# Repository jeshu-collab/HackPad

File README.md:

# HackPad1

HackPad1 is a custom 9-key macropad built using the Seeed XIAO RP2040. It includes a rotary encoder, a 128x32 OLED display, and per-key RGB lighting. The firmware is written using KMK, making it easy to customize key mappings and add new features.

This project was designed from scratch, including the PCB, enclosure, and firmware.

---

## Features

- 9-key mechanical macropad (3x3 layout)
- EC11 rotary encoder for volume control
- 128x32 OLED display
- Per-key RGB using SK6812MINI-E LEDs
- Powered by Seeed XIAO RP2040
- KMK firmware for easy customization
- Custom 2-piece 3D printed enclosure

---

## CAD Model

The enclosure is designed as a two-piece case.

- **Top Shell:** Holds the switches and has the outer frame.
- **Bottom Plate:** Closes the enclosure and supports the PCB.

### Overall View

### Case Assembly

---

## PCB

The PCB was designed in KiCad. It includes the switch matrix, rotary encoder, OLED display connections, RGB LEDs, and the XIAO RP2040.

### Schematic

### PCB Layout

---

## Firmware

The firmware is based on **KMK**.

Current functionality:

- Rotary encoder controls system volume.
- Pressing the encoder mutes/unmutes the audio.
- The 9 keys are currently mapped as number keys (1–9).
- OLED displays a startup message.

Key mappings can be easily changed by editing `main.py`.

---

## Bill of Materials (BOM)

| Component | Quantity |
|-----------|---------:|
| Cherry MX Switches | 9 |
| Keycaps | 9 |
| 1N4148 Diodes | 9 |
| SK6812MINI-E RGB LEDs | 9 |
| 0.91" 128x32 OLED Display | 1 |
| EC11 Rotary Encoder | 1 |
| Seeed XIAO RP2040 | 1 |
| 3D Printed Enclosure | 1 Set |
| M3 Screws *(update after final assembly)* | As Required |

---

## Future Improvements

- Add multiple layers and shortcuts
- OLED status indicators
- RGB lighting effects
- VIA/Vial-style configuration (if supported)
- Improve case design after testing the first prototype

---

## Acknowledgements

This project was built as part of the Hack Club HackPad initiative.

Special thanks to the Hack Club community for the resources and guidance throughout the build.

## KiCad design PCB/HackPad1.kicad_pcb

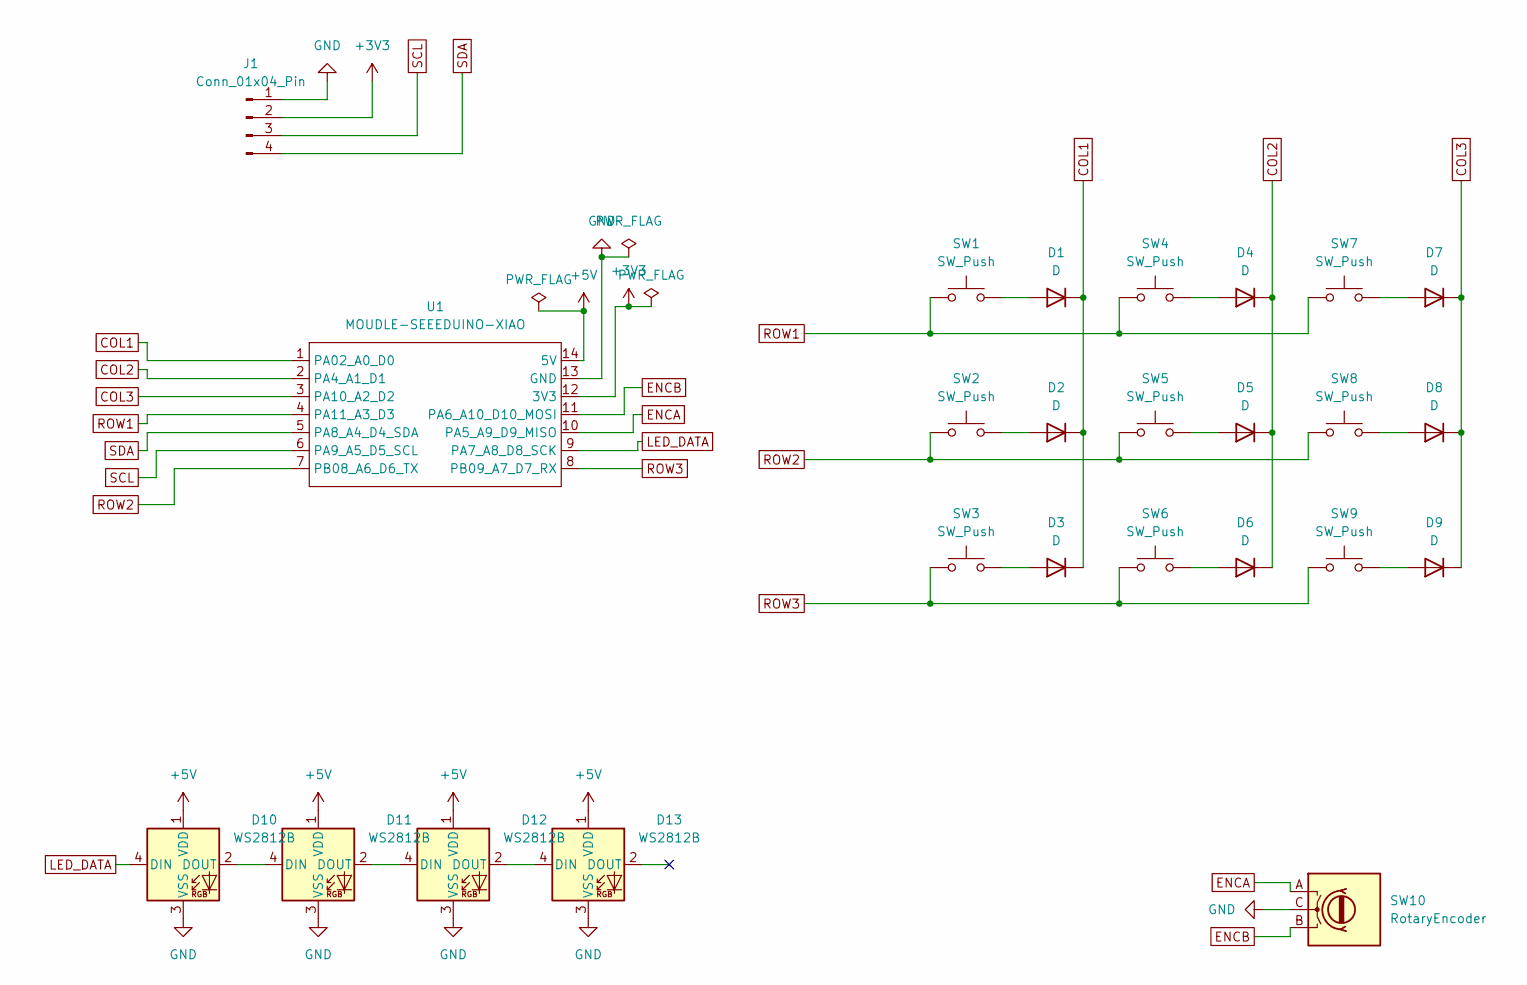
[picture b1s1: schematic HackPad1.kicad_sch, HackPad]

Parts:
D1, D2, D3: D; D_DO-35_SOD27_P7.62mm_Horizontal
D4, D5, D6, D7, D8, D9: D; D_DO-35_SOD27_P10.16mm_Horizontal
D10, D11, D12, D13: WS2812B; MX_SK6812MINI-E
J1: Conn_01x04_Pin; PinSocket_1x04_P2.54mm_Vertical
SW1, SW2, SW3, SW4, SW5, SW6, SW7, SW8, SW9: SW_Push; SW_Cherry_MX_1.00u_PCB
SW10: RotaryEncoder; RotaryEncoder_Alps_EC11E-Switch_Vertical_H20mm
U1: MOUDLE-SEEEDUINO-XIAO; XIAO-Generic-Hybrid-14P-2.54-21X17.8MM

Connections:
+3V3: J1.2, U1.12 (3V3)
+5V: D10.1 (VDD), D11.1 (VDD), D12.1 (VDD), D13.1 (VDD), U1.14 (5V)
COL1: D1.1 (K), D2.1 (K), D3.1 (K), U1.1 (PA02_A0_D0)
COL2: D4.1 (K), D5.1 (K), D6.1 (K), U1.2 (PA4_A1_D1)
COL3: D7.1 (K), D8.1 (K), D9.1 (K), U1.3 (PA10_A2_D2)
ENCA: SW10.A, U1.10 (PA5_A9_D9_MISO)
ENCB: SW10.B, U1.11 (PA6_A10_D10_MOSI)
GND: D10.3 (VSS), D11.3 (VSS), D12.3 (VSS), D13.3 (VSS), J1.1, SW10.C, U1.13 (GND)
LED_DATA: D10.4 (DIN), U1.9 (PA7_A8_D8_SCK)
unnamed: D1.2 (A), SW1.2
unnamed: D2.2 (A), SW2.2
unnamed: D3.2 (A), SW3.2
unnamed: D4.2 (A), SW4.2
unnamed: D5.2 (A), SW5.2
unnamed: D6.2 (A), SW6.2
unnamed: D7.2 (A), SW7.2
unnamed: D8.2 (A), SW8.2
unnamed: D9.2 (A), SW9.2
unnamed: D10.2 (DOUT), D11.4 (DIN)
unnamed: D11.2 (DOUT), D12.4 (DIN)
unnamed: D12.2 (DOUT), D13.4 (DIN)
ROW1: SW1.1, SW4.1, SW7.1, U1.4 (PA11_A3_D3)
ROW2: SW2.1, SW5.1, SW8.1, U1.7 (PB08_A6_D6_TX)
ROW3: SW3.1, SW6.1, SW9.1, U1.8 (PB09_A7_D7_RX)
SCL: J1.3, U1.6 (PA9_A5_D5_SCL)
SDA: J1.4, U1.5 (PA8_A4_D4_SDA)

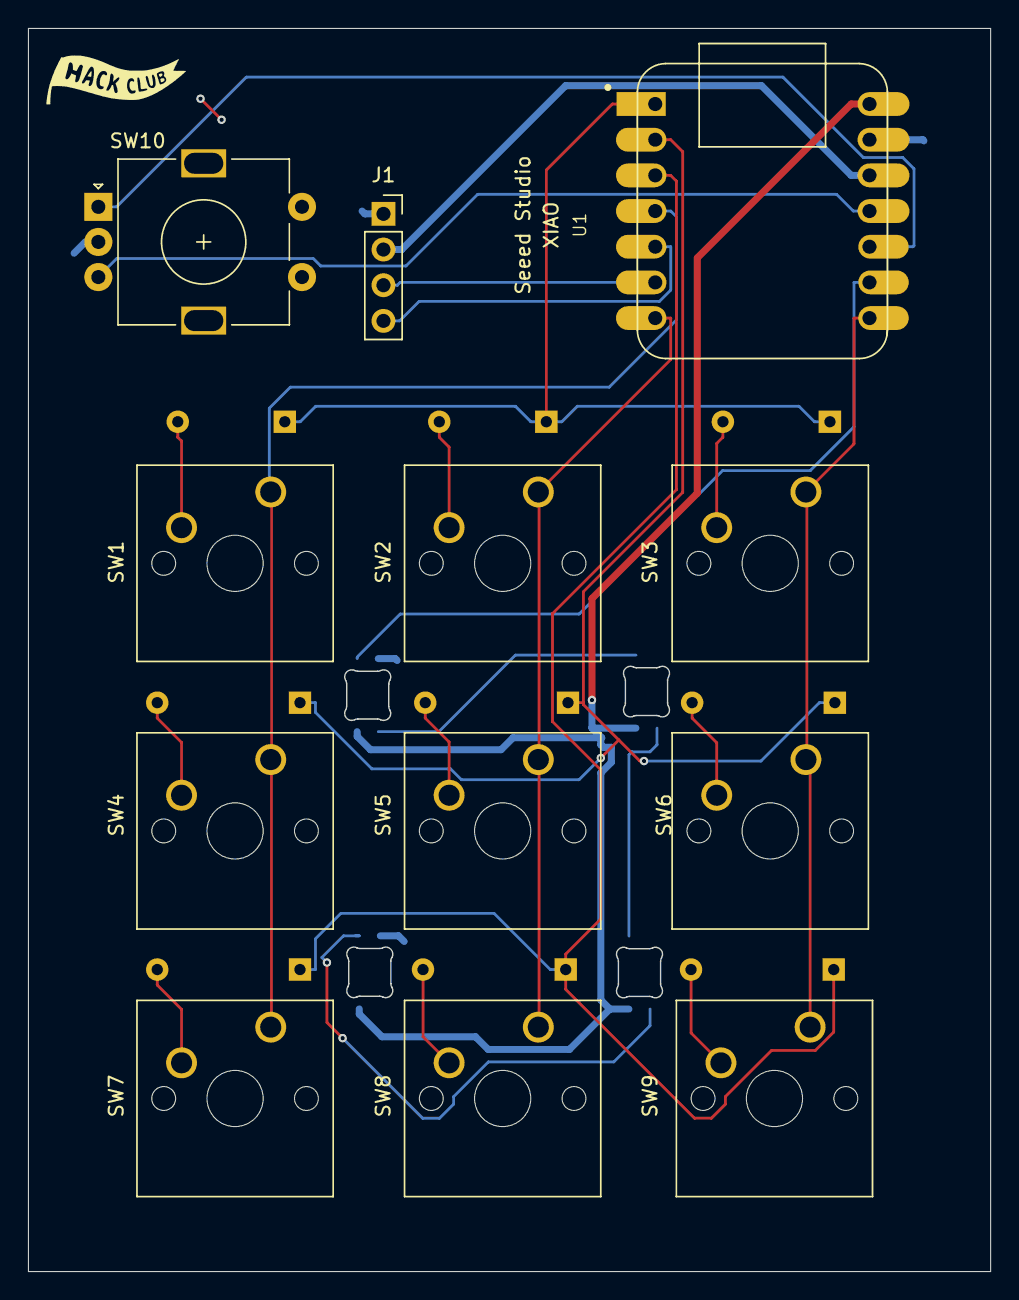
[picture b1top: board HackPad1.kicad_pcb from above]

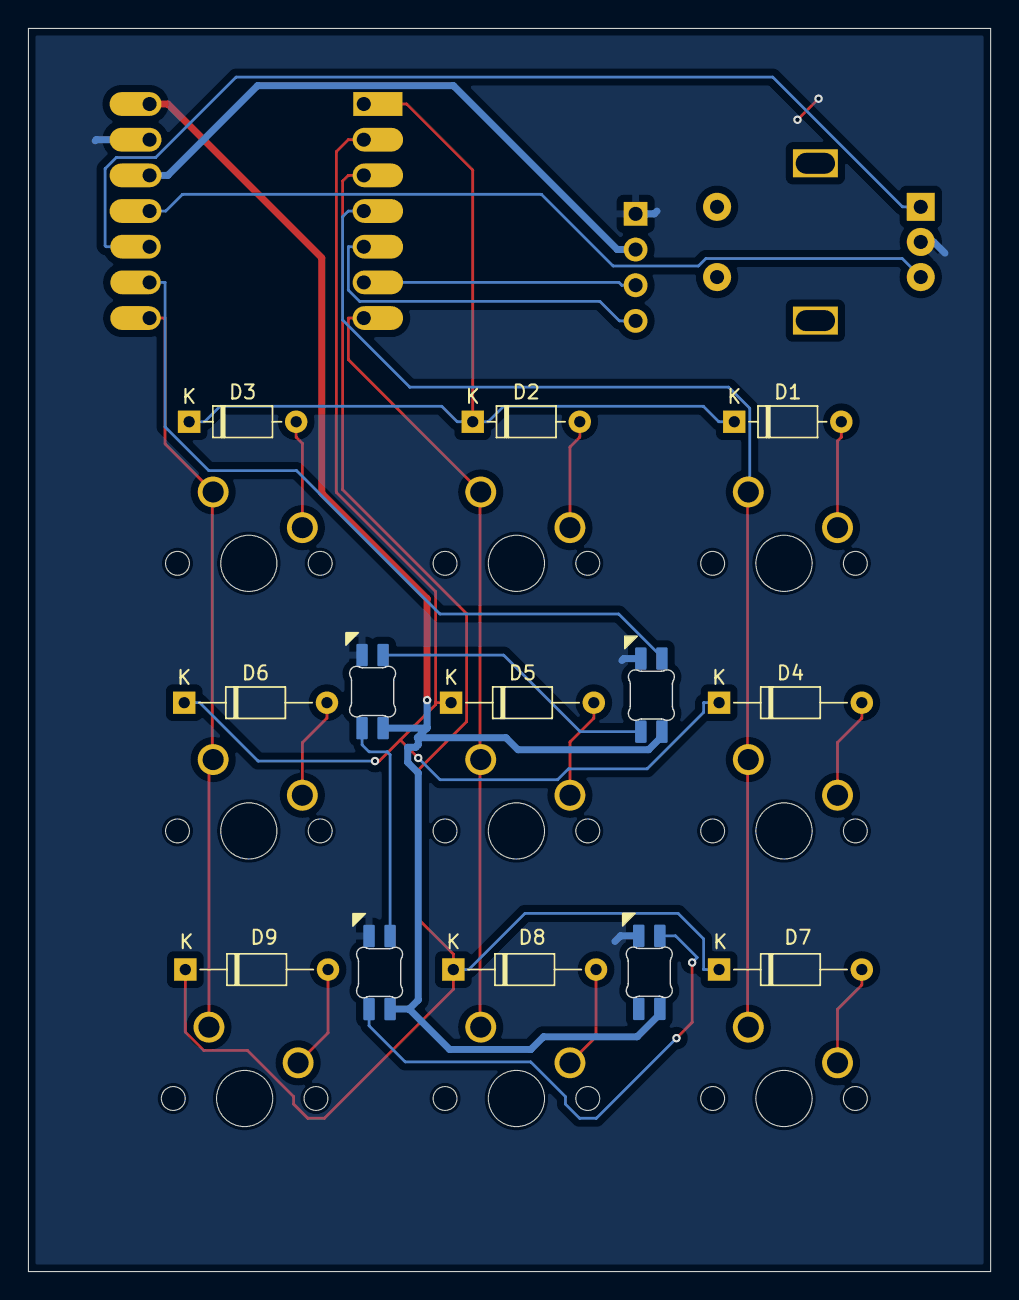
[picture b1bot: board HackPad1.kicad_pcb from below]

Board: 2 copper layers, 68.5 x 88.5 mm, 25 parts (9 on the bottom side), 26 nets.

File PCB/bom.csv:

"Reference","Value","Datasheet","Footprint","Qty","DNP"
"D1,D2,D3,D4,D5,D6,D7,D8,D9","D","~","-- mixed values --","9",""
"D10,D11,D12,D13","WS2812B","https://cdn-shop.adafruit.com/datasheets/WS2812B.pdf","Keyboard_Parts:MX_SK6812MINI-E","4",""
"J1","Conn_01x04_Pin","~","Connector_PinSocket_2.54mm:PinSocket_1x04_P2.54mm_Vertical","1",""
"SW1,SW2,SW3,SW4,SW5,SW6,SW7,SW8,SW9","SW_Push","~","Button_Switch_Keyboard:SW_Cherry_MX_1.00u_PCB","9",""
"SW10","RotaryEncoder","~","Rotary_Encoder:RotaryEncoder_Alps_EC11E-Switch_Vertical_H20mm","1",""
"U1","MOUDLE-SEEEDUINO-XIAO","","footprints:XIAO-Generic-Hybrid-14P-2.54-21X17.8MM","1",""

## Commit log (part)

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2026-06-28 Learning pcb editor for HackPad
2026-06-28 Initial
2026-06-28 Add .gitignore and remove local settings
2026-06-28 pcb basics
2026-06-28 changed layout
2026-06-29 designed pcb routing basics
2026-06-29 design difficulty
2026-06-29 layout 2
2026-06-29 updated design basics
